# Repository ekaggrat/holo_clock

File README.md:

View this project on [CADLAB.io](https://cadlab.io/node/990). 

holo_clock
==========
arduino and pcb files for holo clock

published
http://hackaday.com/2014/12/01/3d-printed-clock-tells-time-with-gears/

3d files here
http://www.thingiverse.com/thing:570797

for sale here
https://www.tindie.com/products/ekaggrat/holo-clock-2/

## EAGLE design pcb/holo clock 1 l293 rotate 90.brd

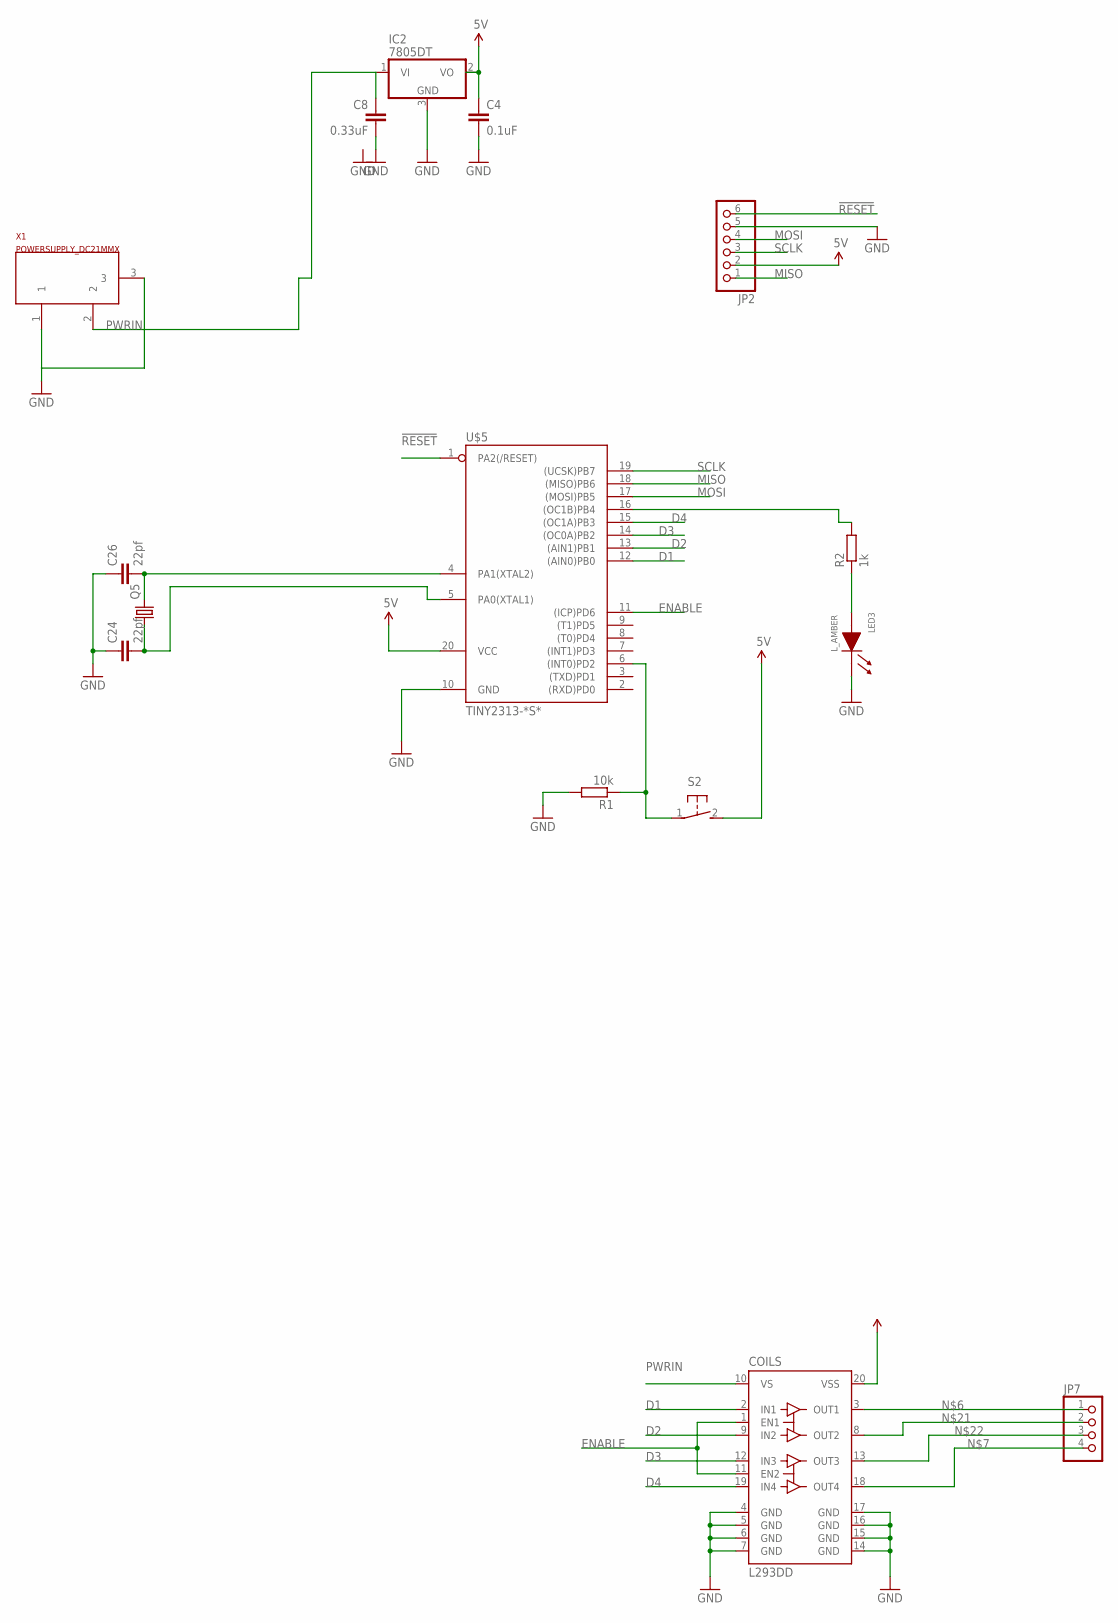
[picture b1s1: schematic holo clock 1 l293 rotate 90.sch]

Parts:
C4: 0.1uF; CAP-PTH-SMALL2
C8: 0.33uF; CAP-PTH-SMALL2
C24, C26: 22pf; 0805
COILS: L293DD; SO20
IC2: 7805DT; TO252
JP2: PINHD-1X6; 1X06
JP7: PINHD-1X04_2.54; 1X04
LED3: L_AMBER; LED0805
Q5: CRYSTALHC49S; HC49/S
R1: 10k; R0805
R2: 1k; R0805
S2: 31-XX; B3F-31XX
U$5: TINY2313-*S*; SO20L$
X1: POWERSUPPLY_DC21MMX; POWERSUPPLY_DC-21MM

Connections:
5V: C4.1, COILS.20 (VSS), IC2.2 (VO), JP2.2, S2.2 (S), U$5.20 (VCC)
!RESET: JP2.6, U$5.1 (PA2(/RESET))
D1: COILS.2 (IN1), U$5.12 ((AIN0)PB0)
D2: COILS.9 (IN2), U$5.13 ((AIN1)PB1)
D3: COILS.12 (IN3), U$5.14 ((OC0A)PB2)
D4: COILS.19 (IN4), U$5.15 ((OC1A)PB3)
ENABLE: COILS.1 (EN1), COILS.11 (EN2), U$5.11 ((ICP)PD6)
GND: C4.2, C8.2, C24.1, C26.1, COILS.4 (GND), COILS.5 (GND), COILS.6 (GND), COILS.7 (GND), COILS.14 (GND), COILS.15 (GND), COILS.16 (GND), COILS.17 (GND), IC2.3 (GND), JP2.5, LED3.1 (CA), R1.2, U$5.10 (GND), X1.1, X1.3
MISO: JP2.1, U$5.18 ((MISO)PB6)
MOSI: JP2.4, U$5.17 ((MOSI)PB5)
unnamed: R2.2, U$5.16 ((OC1B)PB4)
unnamed: COILS.3 (OUT1), JP7.1
unnamed: COILS.18 (OUT4), JP7.4, LED3.2 (AN), R2.1
unnamed: R1.1, S2.1, U$5.6 ((INT0)PD2)
unnamed: COILS.8 (OUT2), JP7.2
unnamed: COILS.13 (OUT3), JP7.3
unnamed: C26.2, Q5.2, U$5.4 (PA1(XTAL2))
unnamed: C24.2, Q5.1, U$5.5 (PA0(XTAL1))
PWRIN: C8.1, COILS.10 (VS), IC2.1 (VI), X1.2
SCLK: JP2.3, U$5.19 ((UCSK)PB7)

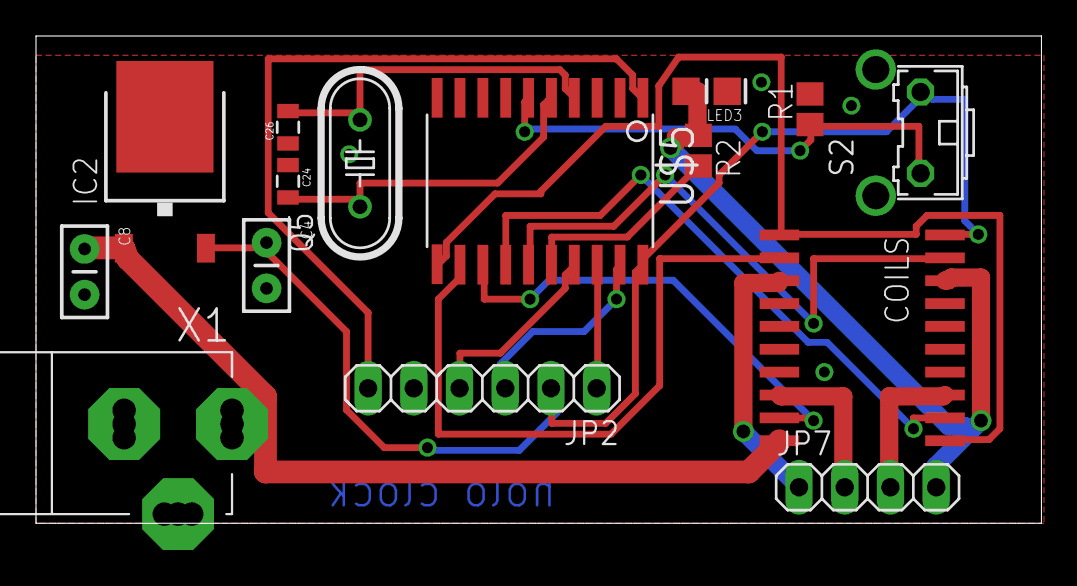
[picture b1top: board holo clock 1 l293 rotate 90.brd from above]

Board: 2 copper layers, 55.9 x 27.1 mm, 15 parts (0 on the bottom side), 20 nets.

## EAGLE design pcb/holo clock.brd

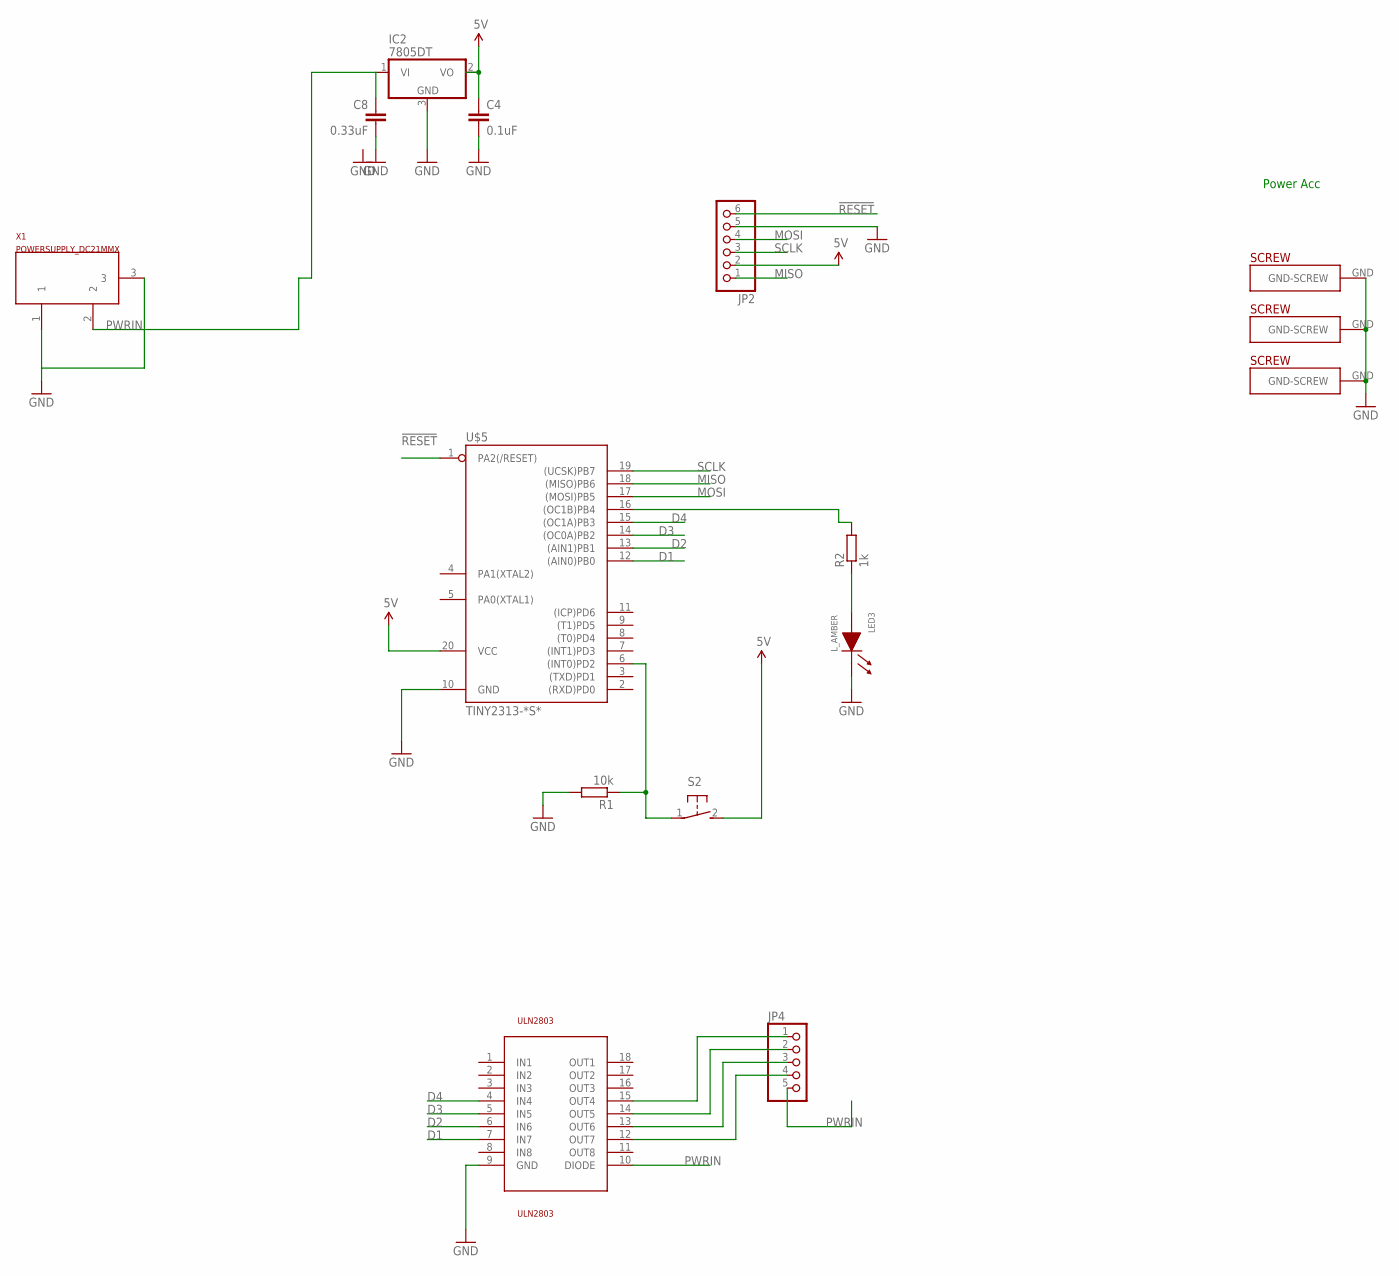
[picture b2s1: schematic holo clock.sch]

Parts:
C4: 0.1uF; CAP-PTH-SMALL2
C8: 0.33uF; CAP-PTH-SMALL2
IC2: 7805DT; TO252
JP2: PINHD-1X6; 1X06
JP4: PINHD-1X5; 1X05
LED3: L_AMBER; LED0805
R1: 10k; R0805
R2: 1k; R0805
S2: 31-XX; B3F-31XX
U$5: TINY2313-*S*; SO20L$
U$14, U$17, U$18: PLATED-SCREW; PLATEDSCREW
ULN2803: ULN2803; SO18L
X1: POWERSUPPLY_DC21MMX; POWERSUPPLY_DC-21MM

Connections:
5V: C4.1, IC2.2 (VO), JP2.2, S2.2 (S), U$5.20 (VCC)
!RESET: JP2.6, U$5.1 (PA2(/RESET))
D1: U$5.12 ((AIN0)PB0), ULN2803.7 (IN7)
D2: U$5.13 ((AIN1)PB1), ULN2803.6 (IN6)
D3: U$5.14 ((OC0A)PB2), ULN2803.5 (IN5)
D4: U$5.15 ((OC1A)PB3), ULN2803.4 (IN4)
GND: C4.2, C8.2, IC2.3 (GND), JP2.5, LED3.1 (CA), R1.2, U$5.10 (GND), U$14.GND, U$17.GND, U$18.GND, ULN2803.9 (GND), X1.1, X1.3
MISO: JP2.1, U$5.18 ((MISO)PB6)
MOSI: JP2.4, U$5.17 ((MOSI)PB5)
unnamed: JP4.1, ULN2803.15 (OUT4)
unnamed: R2.2, U$5.16 ((OC1B)PB4)
unnamed: JP4.2, ULN2803.14 (OUT5)
unnamed: JP4.3, ULN2803.13 (OUT6)
unnamed: JP4.4, ULN2803.12 (OUT7)
unnamed: LED3.2 (AN), R2.1
unnamed: R1.1, S2.1, U$5.6 ((INT0)PD2)
PWRIN: C8.1, IC2.1 (VI), JP4.5, ULN2803.10 (DIODE), X1.2
SCLK: JP2.3, U$5.19 ((UCSK)PB7)

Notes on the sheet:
Power Acc

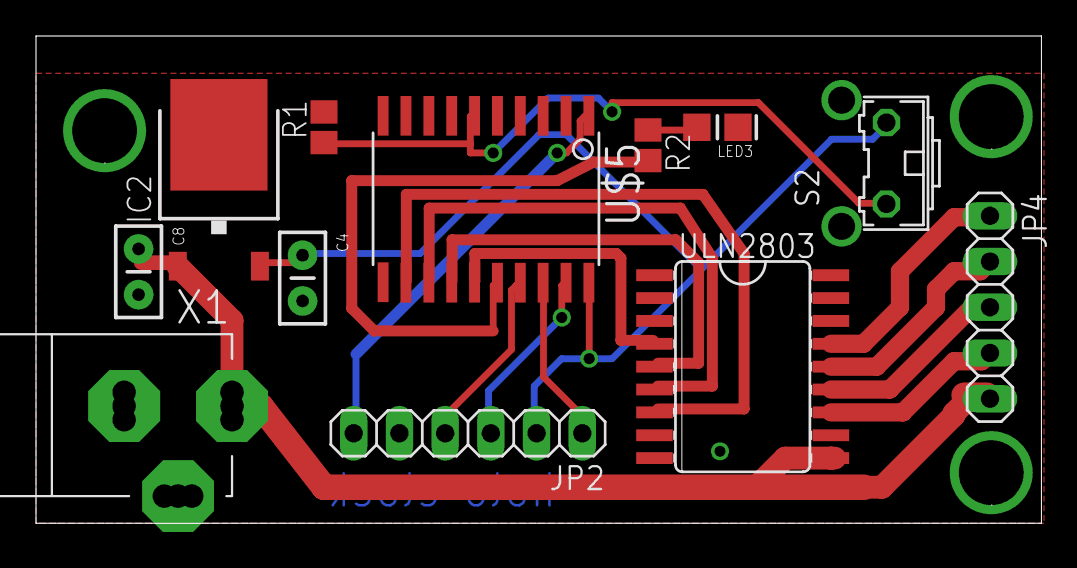
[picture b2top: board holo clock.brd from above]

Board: 2 copper layers, 55.9 x 27.1 mm, 15 parts (0 on the bottom side), 18 nets.

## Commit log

2014-11-30 pcb and ino
2014-12-02 added crystal to pcb
2015-02-12 final pcb
2015-03-24 bipolar motor
2015-03-24 bipolar motor pcb
2016-11-08 reboot
2016-11-14 instructions
2016-11-14 instructionss
2016-11-16 instruct
2017-08-02 pcb track error
    please see this if you make the pcb. The track on the back side of the board needs to be cut or the led will get short.
2018-05-07 Backlink to CADLAB.io has been added.
